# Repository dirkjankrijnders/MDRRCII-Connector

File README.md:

MDRRCII-Connector
=================

This is a small interface board to connect the [Mini STM32 board](http://www.ebay.com/itm/MINI-V3-STM32F103RBT6-development-board-with-2-8-TFT-module-/121287420704?pt=Art_Prints&hash=item1c3d4b2b20) as used in [MDRRC II](http://members.home.nl/robert.evers/mdrrc2.htm) its peripherals. It is effectively all of the schematics in the manual on a nice board. It uses a DIN5 connector for I2C controller and also has a [S88N](http://www.s88-n.eu) pin-compatible RJ45 connection. Its power it receives from a 4-pin molex connector as commonly found in computers. By default this also powers the STM32, which is not desirable unless an USB isolator is used. 

It also includes a USB isolator, not necessary for normal operation, but when fiddling around I'd rather blow the 10 euro isolator than my laptops usb port. It also 

Unchecked Reichelt shopping card:
http://www.reichelt.de/?ACTION=20;AWKID=901501;PROVID=2084

STATUS
------
Board for Rev.0 are on order and recieved. The first board is build and very lightly tested with MDRRC version one, due to a rather lengthy remodeling of my train room (well actually, the creation of...). Below is a photo of the prototype. Testing with MDRRC-II is under way though.

<table>
<tr>
<th>Function</th><th>test</th>
</tr>
<tr><td>Power</td><td>Passed</td></tr>
<tr><td>Booster connection</td><td>Passed</td></tr>
<tr><td>S88N</td><td>Passed*</td></tr>
<tr><td>I2C</td><td>Failed, see issue #1</td></tr>
<tr><td>Programming</td><td>Untested</td></tr>
<tr><td>Expressnet</td><td>Untested</td></tr>
</table>
* Works, but S88N signal specifications remain untested until now.

LICENSE
-------

Both hardware and firmware are placed under the Creative Commons Attribution-ShareAlike 3.0 Unported License. See <http://creativecommons.org/licenses/by-sa/3.0/> and License.txt for more details.

Copyright 2014
Dirkjan Krijnders
<dirkjan@krijnders.net>

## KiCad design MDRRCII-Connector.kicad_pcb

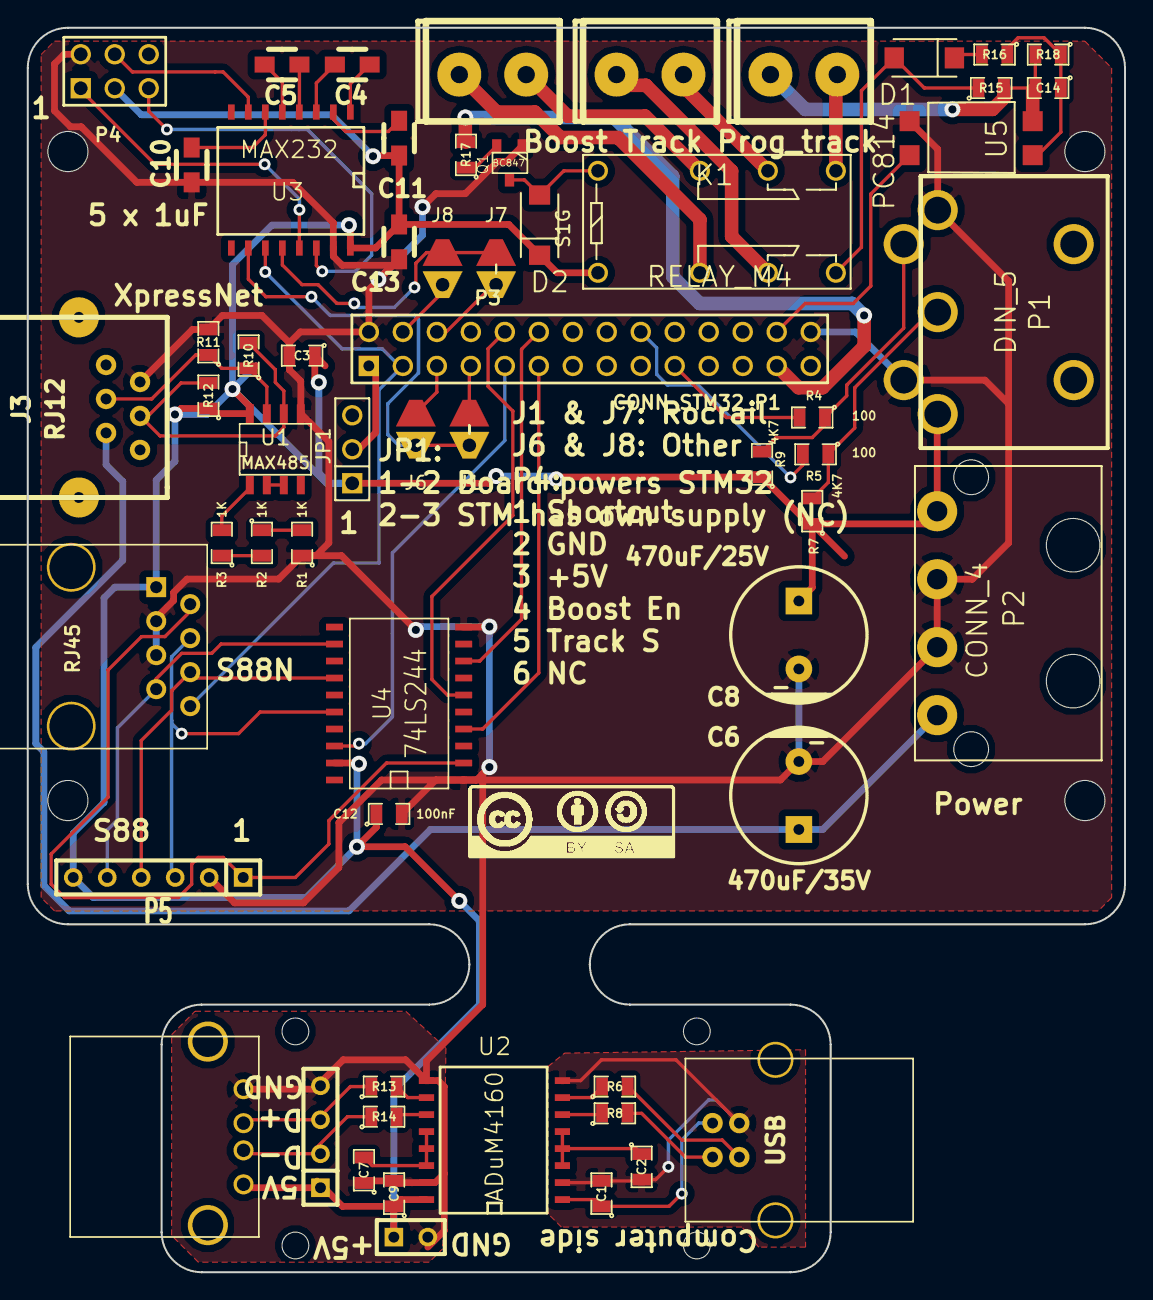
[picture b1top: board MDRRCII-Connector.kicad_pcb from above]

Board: 2 copper layers, 82.0 x 93.0 mm, 68 parts (0 on the bottom side), 63 nets.

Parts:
C1, C2, C3, C7, C9, C12: 100nF; SM0805
C4, C5, C10, C11, C13: 1uF; Capacitor_SMD0805_HandSoldering_RevA_Date21Jun2010
C6: 470uF/35V; CP_10x21mm
C8: 470uF/25V; CP_10x21mm
C14: 33nF; SM0805
D1, D2: S1G; DO-214AC
J1, J7: SOLDER_JUMPER_CONN; solder_jumper_conn
J2: USB; USB_B
J3: RJ12; RJ12_E
J4: USB_2; USB_A
J5: RJ45; RJ45_8
J6, J8: SOLDER_JUMPER; solder_jumper
JP1: JUMPER; PIN_ARRAY_3X1
K1: RELAY_M4; Relais_M4
M2, M2#2, M2#3, M2#4, M2#5, M2#6, M2#7, M2#8: VAL**; M2
P1: DIN_5
P2: CONN_4; MOLEX_15-24-4441
P3: CONN_STM32_P1; pin_array_14x2
P4: CONN_3X2; pin_array_3x2
P5: CONN_6; SIL-6
P6: CONN_2; SIL-2
P7: CONN_4; SIL-4
P8, P9, P10: CONN_2; 2PIN_SC_RM5
Q1: BC847; SOT23
R1, R2, R3, R17: 1K; SM0805
R4, R5: 100; SM0805
R6, R8, R13, R14: 24 1%; SM0805
R7, R9: 4K7; SM0805
R10: 120; SM0805
R11, R12: 1K5; SM0805
R15: 39; SM0805
R16: 680; SM0805
R18: 47k; SM0805
U1: MAX485; SO8E
U2: ADuM4160; SO16W
U3: MAX232; SO16W
U4: 74LS244; SO20L
U5: PC814; 4LD_MDIP

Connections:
+5V: C3.1, C8.1, C9.1, C11.2, C12.1, C13.1, D2.2, J4.4, J5.1, JP1.1, K1.1, P1.3, P2.4, P4.3, P5.6, P6.1, P7.1, R7.1, R9.1, R12.1, U1.8, U2.16, U3.16, U4.19
+12V: C6.1, J3.5, P2.1
ACK_Input: P3.26, U5.4
BOOST1_Brown: K1.3, P8.1
BOOST1_Red: K1.4, P8.2
Booster_SC_232: P4.1, U3.13
Booster_SC_ttl: J7.1, J8.1, U3.12
Booster_enable_232: P4.4, U3.7
Booster_enable_ttl: J1.2, J6.2, U3.10
GND: C3.2, C6.2, C7.1, C8.2, C9.2, C10.1, C12.2, C13.2, J3.2, J4.1, J5.3, J5.5, P1.1, P1.5, P2.2, P2.3, P3.2, P3.28, P4.2, P5.2, P6.2, P7.4, Q1.1, R1.1, R11.2, U1.5, U2.9, U2.15, U3.15, U4.1, U4.10, U5.3
I2C_SCL: P3.18, R5.2
I2C_SDA: P3.19, R4.2
unnamed: D2.1, K1.2, Q1.3
unnamed: Q1.2, R17.1
unnamed: J3.3, R10.1, R11.1, U1.7
unnamed: J3.4, R10.2, R12.2, U1.6
unnamed: R3.2, U1.1
unnamed: R1.2, R2.1
unnamed: P1.2, R5.1, R7.2
unnamed: P1.4, R4.1, R9.2
unnamed: D1.2, R16.2
unnamed: C14.1, R16.1, R18.1, U5.1
unnamed: J8.2, P3.4
unnamed: J1.1, P3.7
unnamed: J6.1, P3.5
unnamed: JP1.2, P3.1
unnamed: J7.2, P3.6
unnamed: C4.2, U3.3
unnamed: C5.2, U3.5
unnamed: J4.3, P7.2, R14.1
unnamed: J4.2, P7.3, R13.1
unnamed: J5.2, P5.1, U4.2
unnamed: J5.4, P5.3, U4.16
unnamed: J5.7, P5.5, U4.12
unnamed: C10.2, U3.6
unnamed: C4.1, U3.1
unnamed: C5.1, U3.4
unnamed: C11.1, U3.2
unnamed: C1.1, J2.1, U2.1
unnamed: R14.2, U2.11
unnamed: R13.2, U2.10
unnamed: C7.2, U2.12, U2.13, U2.14
unnamed: C2.1, U2.3, U2.4, U2.5
unnamed: J5.6, P5.4, U4.14
unnamed: C1.2, C2.2, J2.4, U2.2, U2.8
unnamed: R8.1, U2.6
unnamed: J2.2, R8.2
unnamed: R6.1, U2.7
unnamed: J2.3, R6.2
PA1: U1.2, U1.3
PA2: R2.2, R3.1
ProgTrack_ACK: D1.1, K1.7, R15.1
ProgTrack_Brown: C14.2, P9.1, R15.2, R18.2, U5.2
ProgTrack_Red: K1.8, P9.2
Prog_track_relay: P3.25, R17.2
S88_Clk: P3.11, U4.4
S88_Reset: P3.12, U4.8
S88_data: P3.9, U4.18
S88_shift: P3.10, U4.6
Track1_Brown: K1.5, P10.1
Track1_Red: K1.6, P10.2
Track_signal_232: P4.5, U3.14
Track_signal_ttl: J5.8, P3.3, U3.11

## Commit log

2014-04-21 Rev 0 roughly done
2014-04-21 Rev 0 production files
2014-04-21 Small cleanup on schematic and PDF creation
2014-04-23 Added some SKUs and BOM
2014-04-23 Added license
2014-04-24 Added (unchecked) Reichelt shopping card
2014-04-24 More readme
2014-05-23 Kicad version update
2014-05-23 Silkscreen and mounting holes updated
2014-05-23 Fixed silkscreen around R4, R5, R7 and R9
2014-08-12 Added PDF with the board
2014-08-13 Added picture of build PCB in action
2014-08-13 Updated status
2014-08-13 And the gitignore to reflect the fixed name
2014-08-13 Fixed name
2014-08-29 Fixed I2C line
2014-08-29 Remove bak file from repo
